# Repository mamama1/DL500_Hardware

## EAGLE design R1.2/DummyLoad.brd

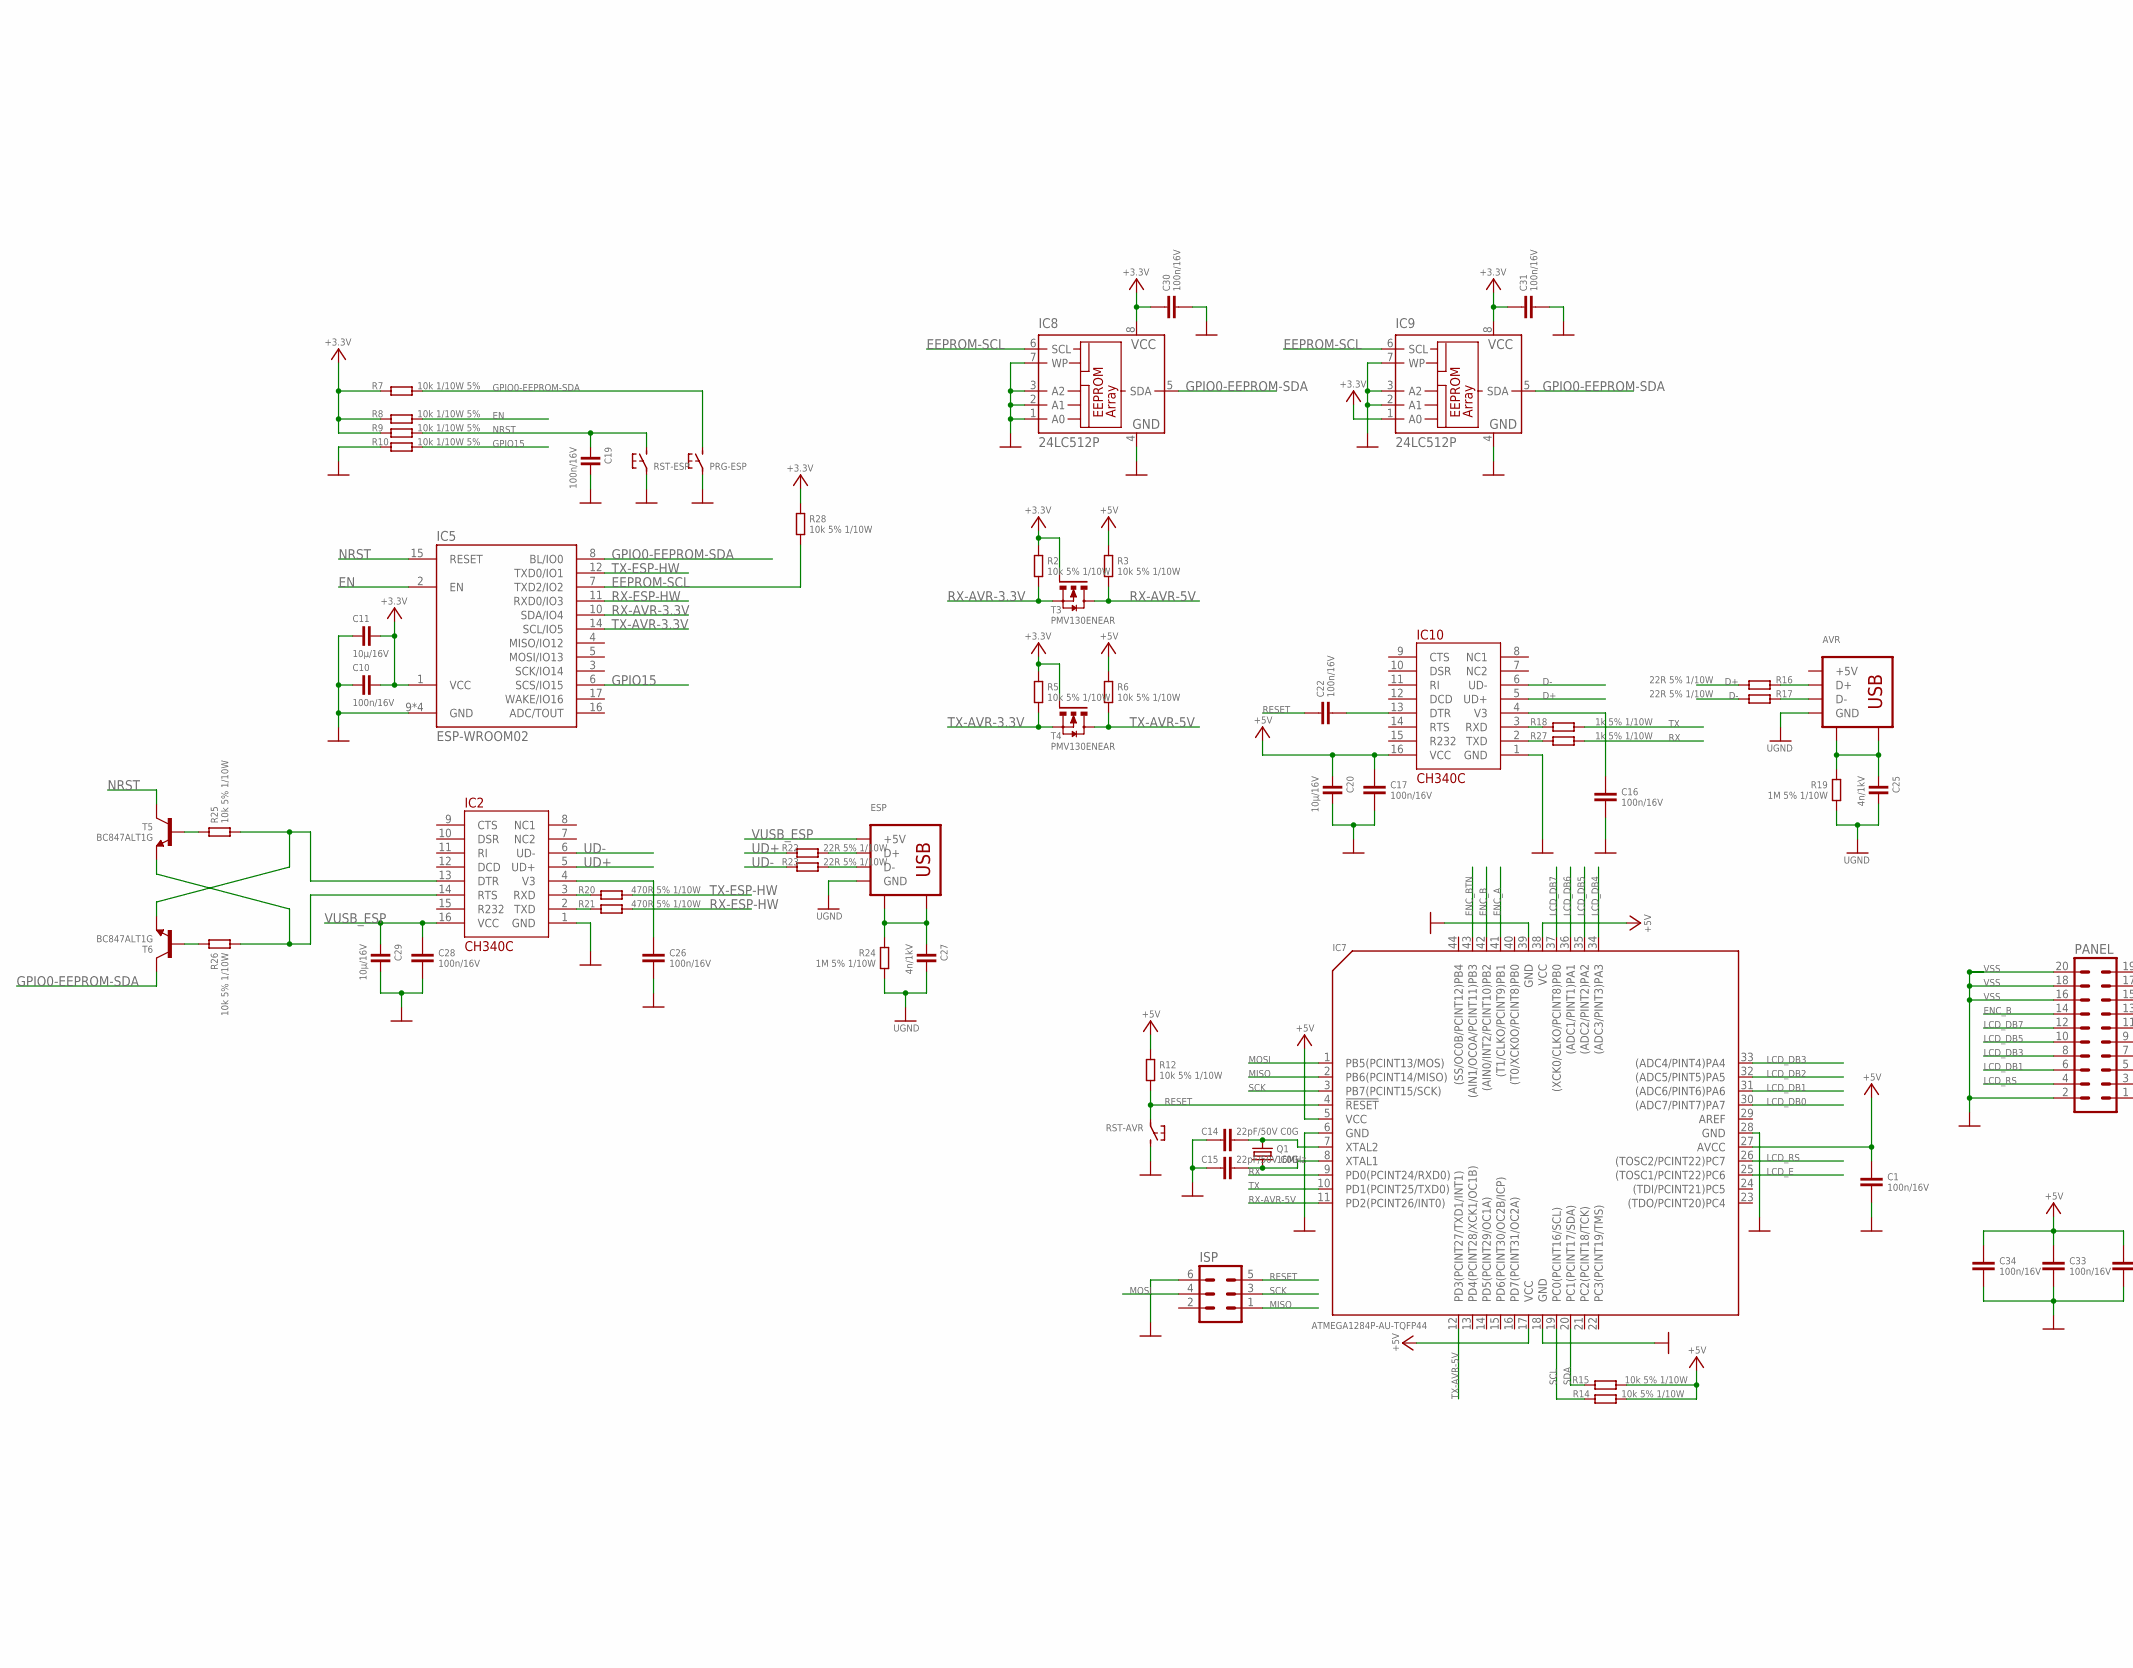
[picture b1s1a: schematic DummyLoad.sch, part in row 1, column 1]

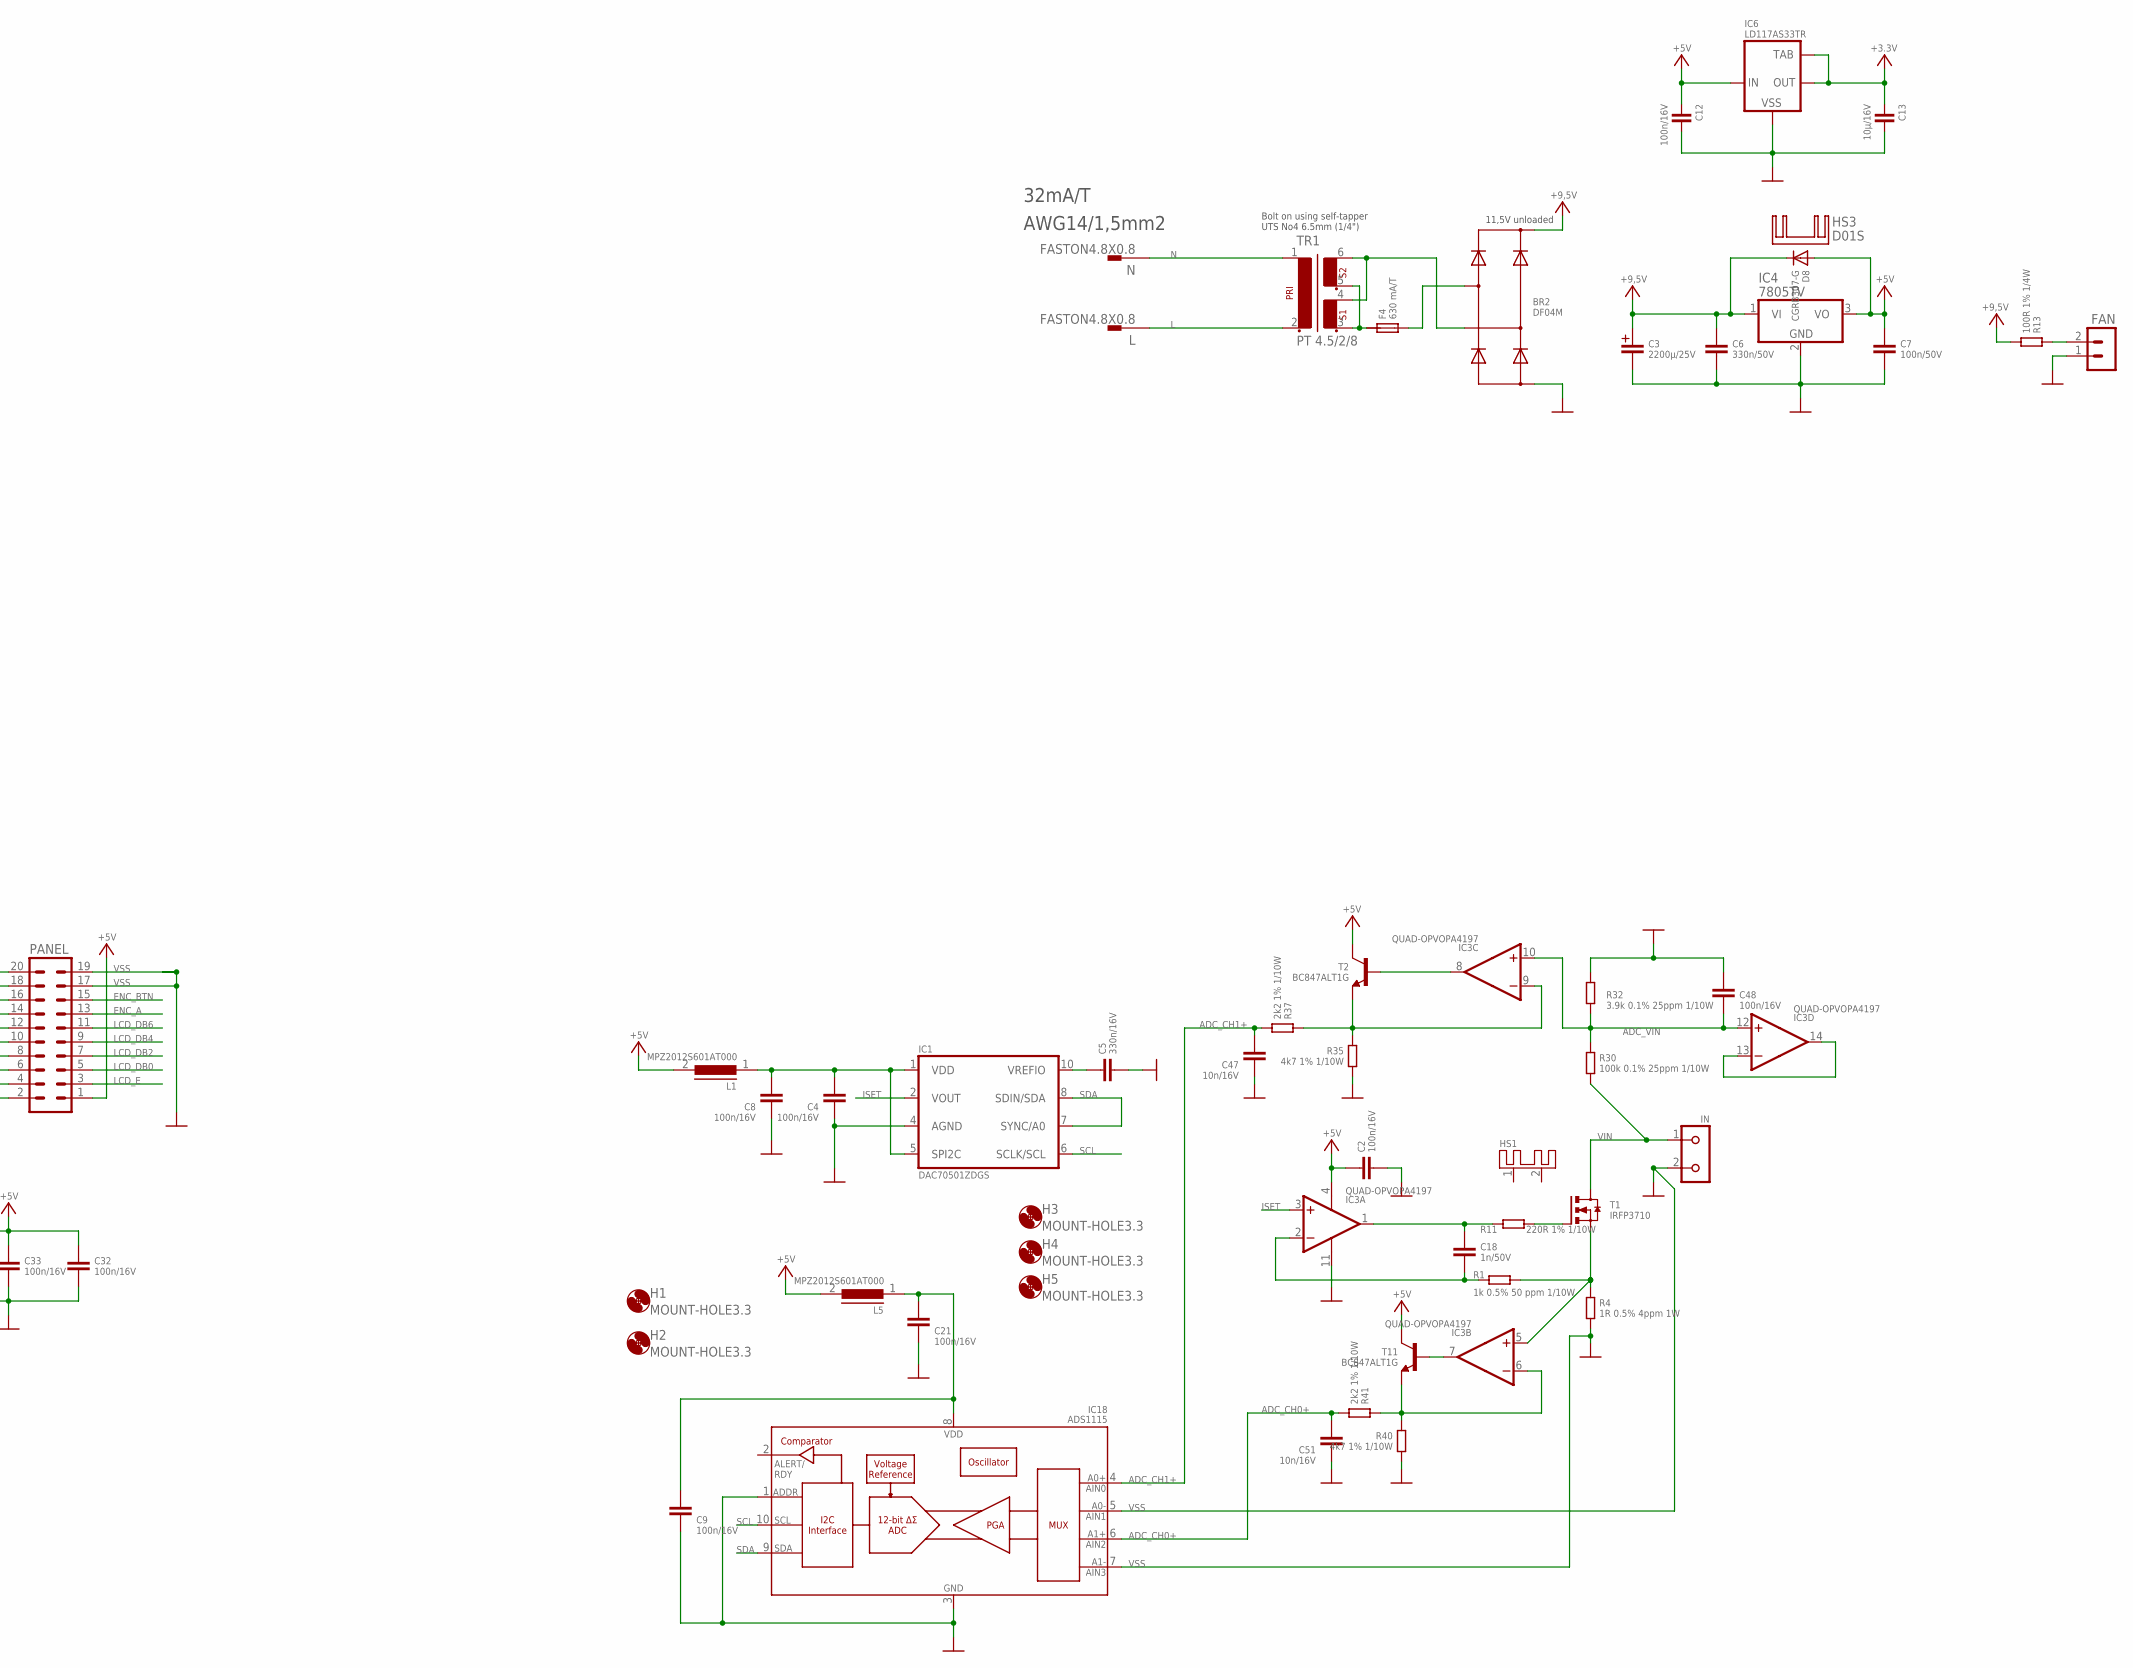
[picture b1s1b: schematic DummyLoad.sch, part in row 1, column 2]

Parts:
AVR: USBUSB-B; USB-B
BR2: DF04M; BR-DIL2
C1, C2, C4, C8, C9, C16, C17, C21, C22, C26, C28, C30, C31, C32, C33, C34, C48: 100n/16V; 0805
C3: 2200µ/25V; C+/5/12.5
C5: 330n/16V; 0805
C6: 330n/50V; 0805
C7: 100n/50V; 0805
C10, C12, C19: 100n/16V; C0805
C11, C13, C20, C29: 10µ/16V; C1210
C14, C15: 22pF/50V C0G; 0805
C18: 1n/50V; 0805
C25, C27: 4n/1kV; C1206
C47, C51: 10n/16V; 0805
D8: CGRB307-G; DO214AA-CGRB307-G
ESP: USBUSB-B; USB-B
F4: 630 mA/T; F5X20
FAN: JST-PH-2.0-2P
H1, H2, H3, H4, H5: MOUNT-HOLE3.3; 3,3
HS1: HSCR201-50; CR201-50
HS3: D01S
IC1: DAC70501ZDGS; VSSOP10
IC2, IC10: CH340C; SOP16
IC3: QUAD-OPVOPA4197; SO14
IC4: 7805TV; TO220V
IC5: ESP-WROOM02
IC6: LD117AS33TR; SOT223
IC7: ATMEGA1284P-AU-TQFP44; TQFP44-0.8-9.6X9.6MM
IC8, IC9: 24LC512P; DIL08
IC18: ADS1115; VSSOP10
IN: KL2691311500002; KL2-691311500002
ISP: ML6
L: FASTON4.8X0.8; FASTON-4.8X0.8
L1, L5: MPZ2012S601AT000; C0805K
N: FASTON4.8X0.8; FASTON-4.8X0.8
PANEL: MA10-2
PRG-ESP: TS1B3F-10XX; B3F-10XX
Q1: 16MHz; Q-5X3.2MM-TXC-7A.SERIES
R1: 1k 0.5% 50 ppm 1/10W; C0805K
R2, R3, R5, R6, R12, R14, R15, R25, R26, R28: 10k 5% 1/10W; C0805K
R4: 1R 0.5% 4ppm 1W; R-SHUNT-VSR
R7, R8, R9, R10: 10k 1/10W 5%; C0805K
R11: 220R 1% 1/10W; C0805K
R13: 100R 1% 1/4W; C0805K
R16, R17, R22, R23: 22R 5% 1/10W; C0805K
R18, R27: 1k 5% 1/10W; C0805K
R19, R24: 1M 5% 1/10W; C0805K
R20, R21: 470R 5% 1/10W; C0805K
R30: 100k 0.1% 25ppm 1/10W; C0805K
R32: 3.9k 0.1% 25ppm 1/10W; C0805K
R35, R40: 4k7 1% 1/10W; C0805K
R37, R41: 2k2 1% 1/10W; C0805K
RST-AVR: TS1B3F-10XX; B3F-10XX
RST-ESP: TS1B3F-10XX; B3F-10XX
T1: IRFP3710; TOP3AV
T2, T5, T6, T11: BC847ALT1G; SOT23-BEC
T3, T4: PMV130ENEAR; SOT23
TR1: PT 4.5/2/8; PT/4,5/2/..

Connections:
+3.3V: C10.2, C11.2, C13.1, C30.1, C31.1, IC5.1 (VCC), IC6.2 (OUT), IC6.4 (OUT1), IC8.8 (VCC), IC9.1 (A0), IC9.8 (VCC), R2.1, R5.1, R7.1, R8.1, R9.1, R28.1, T3.1 (G), T4.1 (G)
+5V: C1.1, C2.1, C7.1, C12.1, C17.1, C20.1, C32.1, C33.1, C34.1, D8.A, IC3.4 (V+), IC4.3 (VO), IC6.3 (IN), IC7.5 (VCC), IC7.17 (VCC), IC7.27 (AVCC), IC7.38 (VCC), IC10.16 (VCC), L1.2, L5.2, PANEL.1, R3.1, R6.1, R12.1, R14.2, R15.2, T2.C, T11.C
+9,5V: BR2.DC+, C3.+, C6.1, D8.C, IC4.1 (VI), R13.2
ADC_CH0+: C51.1, IC18.6 (AIN2), R41.2
ADC_CH1+: C47.1, IC18.4 (AIN0), R37.2
ADC_VIN: C48.2, IC3.10 (+IN), IC3.12 (+IN), R30.1, R32.2
D+: IC10.5 (UD+), R16.1
D-: IC10.6 (UD-), R17.1
EEPROM-SCL: IC5.7 (TXD2/IO2), IC8.6 (SCL), IC9.6 (SCL), R28.2
EN: IC5.2 (EN), R8.2
ENC_A: IC7.41 ((T1/CLKO/PCINT9)PB1), PANEL.13
ENC_B: IC7.42 ((AIN0/INT2/PCINT10)PB2), PANEL.14
ENC_BTN: IC7.43 ((AIN1/OCOA/PCINT11)PB3), PANEL.15
GPIO0-EEPROM-SDA: IC5.8 (BL/IO0), IC8.5 (SDA), IC9.5 (SDA), PRG-ESP.3 (2), R7.2, T6.C
GPIO15: IC5.6 (SCS/IO15), R10.2
ISET: IC1.2 (VOUT), IC3.3 (+IN)
L: L.A1, L.A2, TR1.2
LCD_DB0: IC7.30 ((ADC7/PINT7)PA7), PANEL.5
LCD_DB1: IC7.31 ((ADC6/PINT6)PA6), PANEL.6
LCD_DB2: IC7.32 ((ADC5/PINT5)PA5), PANEL.7
LCD_DB3: IC7.33 ((ADC4/PINT4)PA4), PANEL.8
LCD_DB4: IC7.34 ((ADC3/PINT3)PA3), PANEL.9
LCD_DB5: IC7.35 ((ADC2/PINT2)PA2), PANEL.10
LCD_DB6: IC7.36 ((ADC1/PINT1)PA1), PANEL.11
LCD_DB7: IC7.37 ((XCK0/CLKO/PCINT8)PB0), PANEL.12
LCD_E: IC7.25 ((TOSC1/PCINT22)PC6), PANEL.3
LCD_RS: IC7.26 ((TOSC2/PCINT22)PC7), PANEL.4
MISO: IC7.2 (PB6(PCINT14/MISO)), ISP.1
MOSI: IC7.1 (PB5(PCINT13/MOS)), ISP.4
N: N.A1, N.A2, TR1.1
unnamed: C18.1, IC3.1 (OUT), R11.1
unnamed: IC3.7 (OUT), T11.B
unnamed: C16.1, IC10.4 (V3)
unnamed: C18.2, IC3.2 (-IN), R1.2
unnamed: IC3.5 (+IN), R1.1, R4.1, T1.E (S)
unnamed: C9.1, C21.1, IC18.8 (VDD), L5.1
unnamed: C5.1, IC1.10 (VREFIO)
unnamed: IC3.8 (OUT), T2.B
unnamed: IC3.13 (-IN), IC3.14 (OUT)
unnamed: AVR.D+, R16.2
unnamed: AVR.D-, R17.2
unnamed: R11.2, T1.B (G)
unnamed: IC10.3 (RXD), R18.1
unnamed: C14.2, IC7.7 (XTAL2), Q1.2
unnamed: C15.2, IC7.8 (XTAL1), Q1.1
unnamed: IC10.2 (TXD), R27.1
unnamed: AVR.SH1, AVR.SH2, C25.1, R19.1
unnamed: C26.1, IC2.4 (V3)
unnamed: IC2.3 (RXD), R20.1
unnamed: IC2.2 (TXD), R21.1
unnamed: ESP.D+, R22.2
unnamed: ESP.D-, R23.2
unnamed: C27.1, ESP.SH1, ESP.SH2, R24.1
unnamed: R25.1, T5.B
unnamed: R26.1, T6.B
unnamed: C22.2, IC10.13 (DTR)
unnamed: BR2.AC1, F4.3 (2), F4.4 (2)
unnamed: IC2.14 (RTS), R26.2, T5.E
unnamed: IC2.13 (DTR), R25.2, T6.E
unnamed: F4.1, F4.2 (1), TR1.3, TR1.5
unnamed: BR2.AC2, TR1.4, TR1.6
unnamed: FAN.2, R13.1
unnamed: IC3.9 (-IN), R35.1, R37.1, T2.E
unnamed: IC3.6 (-IN), R40.1, R41.1, T11.E
NRST: C19.1, IC5.15 (RESET), R9.2, RST-ESP.3 (2), T5.C
RESET: C22.1, IC7.4 (!RESET), ISP.5, R12.2, RST-AVR.1
RX: IC7.9 (PD0(PCINT24/RXD0)), R27.2
RX-AVR-3.3V: IC5.10 (SDA/IO4), R2.2, T3.2 (S)
RX-AVR-5V: IC7.11 (PD2(PCINT26/INT0)), R3.2, T3.3 (D)
RX-ESP-HW: IC5.11 (RXD0/IO3), R21.2
SCK: IC7.3 (PB7(PCINT15/SCK)), ISP.3
SCL: IC1.6 (SCLK/SCL), IC7.19 (PC0(PCINT16/SCL)), IC18.10 (SCL), R14.1
SDA: IC1.7 (SYNC/A0), IC1.8 (SDIN/SDA), IC7.20 (PC1(PCINT17/SDA)), IC18.9 (SDA), R15.1
TX: IC7.10 (PD1(PCINT25/TXD0)), R18.2
TX-AVR-3.3V: IC5.14 (SCL/IO5), R5.2, T4.2 (S)
TX-AVR-5V: IC7.12 (PD3(PCINT27/TXD1/INT1)), R6.2, T4.3 (D)
TX-ESP-HW: IC5.12 (TXD0/IO1), R20.2
UD+: IC2.5 (UD+), R22.1
UD-: IC2.6 (UD-), R23.1
UGND: AVR.GND, C25.2, C27.2, ESP.GND, R19.2, R24.2
VDD: C4.1, C8.1, IC1.1 (VDD), IC1.5 (SPI2C), L1.1
VIN: IN.1, R30.2, T1.C (D)
VSS: BR2.DC-, C1.2, C2.2, C3.-, C4.2, C5.2, C6.2, C7.2, C8.2, C9.2, C10.1, C11.1, C12.2, C13.2, C14.1, C15.1, C16.2, C17.2, C19.2, C20.2, C21.2, C26.2, C28.2, C29.2, C30.2, C31.2, C32.2, C33.2, C34.2, C47.2, C48.1, C51.2, FAN.1, IC1.4 (AGND), IC2.1 (GND), IC3.11 (V-), IC4.2 (GND), IC5.9 (GND), IC5.13 (GND), IC5.18 (GND), IC5.TP (GND), IC6.1 (VSS), IC7.6 (GND), IC7.18 (GND), IC7.28 (GND), IC7.39 (GND), IC8.1 (A0), IC8.2 (A1), IC8.3 (A2), IC8.4 (GND), IC8.7 (WP), IC9.2 (A1), IC9.3 (A2), IC9.4 (GND), IC9.7 (WP), IC10.1 (GND), IC18.1 (ADDR), IC18.3 (VSS), IC18.5 (AIN1), IC18.7 (AIN3), IN.2, ISP.6, PANEL.2, PANEL.16, PANEL.17, PANEL.18, PANEL.19, PANEL.20, PRG-ESP.1, R4.2, R10.1, R32.1, R35.2, R40.2, RST-AVR.3 (2), RST-ESP.1
VUSB_ESP: C28.1, C29.1, ESP.+5V, IC2.16 (VCC)

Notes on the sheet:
11,5V unloaded
AWG14/1,5mm2
32mA/T
Bolt on using self-tapper UTS No4 6.5mm (1/4")

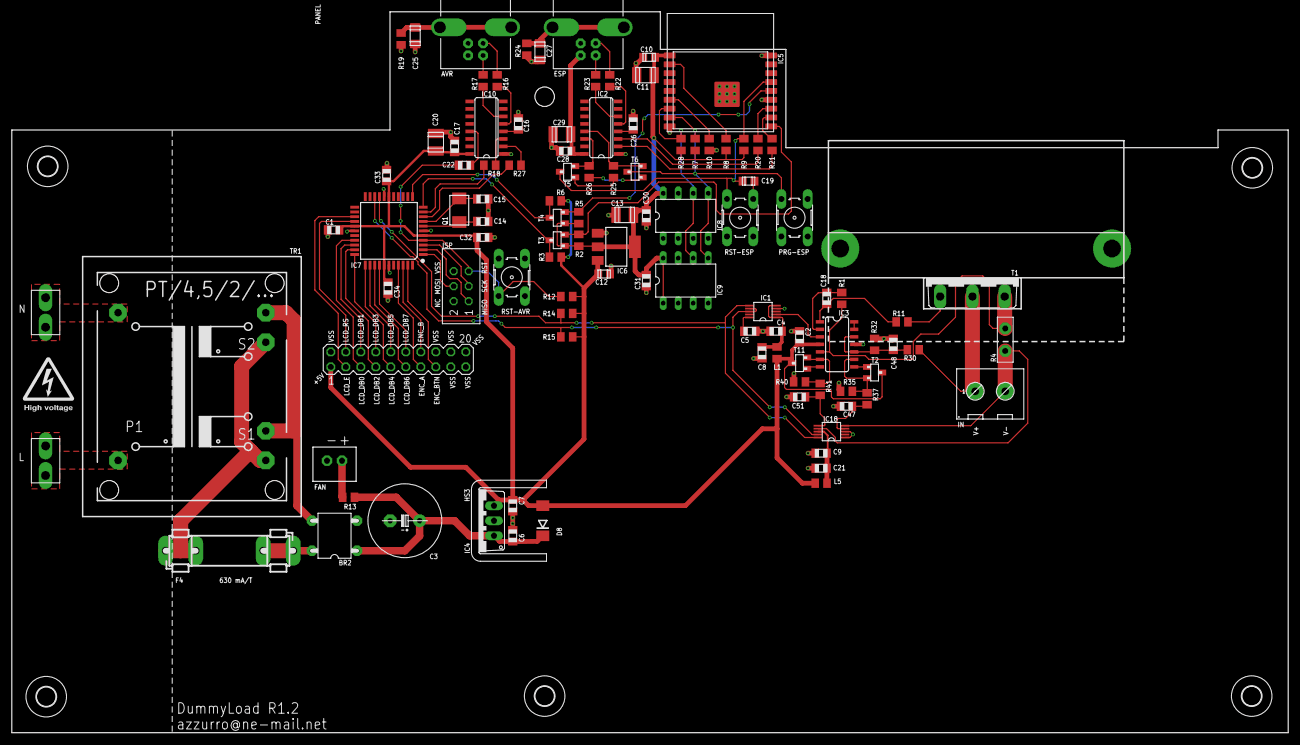
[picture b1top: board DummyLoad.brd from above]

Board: 2 copper layers, 216.0 x 122.0 mm, 116 parts (0 on the bottom side), 84 nets.

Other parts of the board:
U$1: CASE-Z17
U$2: IEC-C14-FUSED-6200.2200
U$3: FAN60X25
U$4: SWITCH-ROCKER-1858.1103

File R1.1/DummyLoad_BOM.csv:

"Qty";"Value";"Device";"Package";"Parts";"Description";"MF";"MPN";"OC_CONRAD";"OC_CONRAD_ADD";"OC_DIGIKEY";"OC_FARNELL";"OC_MOUSER";"OC_MOUSER_ADD";"OC_MOUSER_ADD2";"OC_MOUSER_ALT";"OC_NEWARK";"OC_RS";"OC_RS_ADD";
"1";"";"HSCR201-50";"CR201-50";"HS1";"";"";"";"";"";"";"";"588-CR201-50VE";"588-CLA-TO-21E";"";"";"";"";"";
"1";"";"JST-PH-2.0-2P";"JST-PH-2.0-2P";"FAN";"PIN HEADER";"";"";"";"";"455-1704-ND";"";"";"369-MF60251V21UA99";"";"";"";"";"";
"1";"";"KL2691311500002";"KL2-691311500002";"IN";"Printklemme 2-polig";"";"";"";"";"";"";"710-691311500002";"565-72912-2";"565-6883";"";"";"";"";
"1";"";"MA10-2";"MA10-2";"PANEL";"PIN HEADER";"";"";"";"";"";"unknown";"200-HTSW10907LMD";"";"";"";"unknown";"";"";
"1";"";"ML6";"ML6";"ISP";"HARTING";"";"";"";"";"";"unknown";"200-TSW10307TD";"";"";"";"unknown";"";"";
"3";"";"TS1B3F-10XX";"B3F-10XX";"PRG-ESP, RST-AVR, RST-ESP";"";"";"";"";"";"";"";"653-B3F-1022";"";"";"";"";"";"";
"2";"";"USBUSB-B";"USB-B";"AVR, ESP";"";"";"";"";"";"";"";"";"";"";"";"";"674-1328";"";
"1";"100R 1% 1/4W";"R-SMD0805";"C0805K";"R13";"R";"";"";"";"";"";"";"660-RK73H2ATTD75R0F";"";"";"";"";"";"";
"1";"100k 0.1% 25ppm 1/10W";"R-SMD0805";"C0805K";"R30";"R";"";"";"";"";"";"";"754-RG2012P-104-B-T5";"";"";"";"";"";"";
"3";"100n/16V";"CAPACITOR-0805";"C0805";"C10, C12, C19";"Capacitors";"";"";"";"";"";"";"810-C2012X7R2A104K";"";"";"";"";"";"";
"16";"100n/16V";"CC/0805";"0805";"C1, C2, C4, C8, C9, C16, C17, C20, C21, C22, C23, C26, C28, C30, C31, C48";"Kondensator";"";"";"";"";"";"";"810-C2012X7R2A104K";"";"";"";"";"";"";
"1";"100n/50V";"CC/0805";"0805";"C7";"Kondensator";"";"";"";"";"";"";"810-C2012X7R2A104K";"";"";"";"";"";"";
"4";"10k 1/10W 5%";"R-SMD0805";"C0805K";"R7, R8, R9, R10";"R";"";"";"";"";"";"";"652-CR0805-JW-103ELF";"";"";"";"";"";"";
"11";"10k 5% 1/10W";"R-SMD0805";"C0805K";"R2, R3, R5, R6, R12, R14, R15, R18, R25, R26, R28";"R";"";"";"";"";"";"";"652-CR0805-JW-103ELF";"";"";"";"";"";"";
"2";"10n/16V";"CC/0805";"0805";"C47, C51";"Kondensator";"";"";"";"";"";"";"80-C0805C103K1R";"";"";"";"";"";"";
"4";"10µ/16V";"CAPACITOR-1210";"C1210";"C11, C13, C24, C29";"Capacitors";"";"";"";"";"";"";"963-UMK316BBJ106KL-T";"";"";"";"";"";"";
"1";"16MHz";"Q5X3.2MM-TXC-7A-SERIES";"Q-5X3.2MM-TXC-7A.SERIES";"Q1";"";"";"";"";"";"";"";"717-7A-16.000MAAJ-T";"";"";"";"";"";"";
"2";"1M 5% 1/10W";"R-SMD0805";"C0805K";"R19, R24";"R";"";"";"";"";"";"";"652-CR0805JW-105ELF";"";"";"";"";"";"";
"1";"1R 0.5% 4ppm 1W";"R-SHUNTVSR";"R-SHUNT-VSR";"R4";"";"";"";"";"";"";"";"71-VSRT1R0000DB";"";"";"";"";"";"";
"1";"1k 0.5% 50 ppm 1/10W";"R-SMD0805";"C0805K";"R1";"R";"";"";"";"";"";"";"754-RR1220P-102D";"";"";"";"";"";"";
"1";"1n/50V";"CC/0805";"0805";"C18";"Kondensator";"";"";"";"";"";"";"603-CC805KRX7R0BB102";"";"";"";"";"";"";
"1";"1µ/35V";"CC/0805";"0805";"C32";"Kondensator";"";"";"";"";"";"";"963-UMK212B7105KG-T";"";"";"";"";"";"";
"1";"2200µ/25V";"C+5/12.5";"C+/5/12.5";"C3";"";"";"";"";"";"";"";"667-EEU-FS1E222";"";"";"";"";"";"";
"1";"220R 1% 1/10W";"R-SMD0805";"C0805K";"R11";"R";"";"";"";"";"";"";"652-CR0805FX-2201ELF";"";"";"";"";"";"";
"4";"22R 5% 1/10W";"R-SMD0805";"C0805K";"R16, R17, R22, R23";"R";"";"";"";"";"";"";"652-CR0805JW-220ELF";"";"";"";"";"";"";
"2";"22pF/50V C0G";"CC/0805";"0805";"C14, C15";"Kondensator";"";"";"";"";"";"";"603-CC805JRNPO9BN220";"";"";"";"";"";"";
"2";"24LC512P";"24LC256P";"DIL8";"IC8, IC9";"Serial EEPROM";"MICROCHIP";"24LC256-E/P";"";"";"";"9757970";"579-24LC512-E/P";"";"";"";"92C7169";"";"";
"2";"2k2 1% 1/10W";"R-SMD0805";"C0805K";"R37, R41";"R";"";"";"";"";"";"";"652-CR0805FX-2201ELF";"";"";"";"";"";"";
"1";"3.9k 0.1% 25ppm 1/10W";"R-SMD0805";"C0805K";"R32";"R";"";"";"";"";"";"";"754-RG2012P-392-BT5";"";"";"";"";"";"";
"1";"330n/16V";"CC/0805";"0805";"C5";"Kondensator";"";"";"";"";"";"";"80-C0805C334K5RECTU";"";"";"";"";"";"";
"1";"330n/50V";"CC/0805";"0805";"C6";"Kondensator";"";"";"";"";"";"";"80-C0805C334K5RECTU";"";"";"";"";"";"";
"2";"470R 5% 1/10W";"R-SMD0805";"C0805K";"R20, R21";"R";"";"";"";"";"";"";"652-CR0805FX-4700ELF";"";"";"";"";"";"";
"2";"4k7 1% 1/10W";"R-SMD0805";"C0805K";"R35, R40";"R";"";"";"";"";"";"";"652-CR0805FX-4701ELF";"";"";"";"";"";"";
"2";"4n/1kV";"CAPACITOR-1206";"C1206";"C25, C27";"Capacitors";"";"";"";"";"";"";"581-1206AC392K";"";"";"";"";"";"";
"1";"630 mA/T";"F5X20";"F5X20";"F4";"Sicherung";"";"";"";"";"";"";"693-0751.0110";"";"";"";"";"";"";
"1";"7805TV";"7805TV";"TO220V";"IC4";"Positive VOLTAGE REGULATOR";"";"";"";"";"";"";"511-L7805CV";"";"";"";"";"";"";
"1";"ADS1115";"ADS1015VSSOP10";"VSSOP10";"IC18";"ADS1015 12-BIT ADC";"";"";"";"";"";"";"595-ADS1115IDGSR";"";"";"";"";"";"";
"1";"ATMEGA32U4-AU";"ATMEGA32U4-AU";"TQFP44";"IC7";"Atmel ATmega16U4/32U4 AVR Microcontroller";"";"";"";"";"";"";"556-ATMEGA32U4-AU";"";"";"";"";"";"";
"4";"BC847ALT1G";"T-NPNSOT23-BEC";"SOT23-BEC";"T2, T5, T6, T11";"NPN Transistor";"";"";"";"";"";"";"863-BC847ALT1G";"";"";"";"";"";"";
"1";"CGRB307-G";"DWIDE";"DO214AA-CGRB307-G";"D8";"";"";"";"";"";"";"";"750-CGRB307-G";"";"";"";"";"";"";
"1";"CH340C";"CH340C";"SOP16";"IC2";"";"";"";"";"";"";"";"C84681";"";"";"";"";"";"";
"1";"D01S";"D01S";"D01S";"HS3";"HEATSINK";"";"";"";"";"";"";"532-576802B00";"";"";"";"";"";"";
"1";"DAC70501ZDGS";"DAC70501";"VSSOP10";"IC1";"";"";"";"";"";"";"";"595-DAC70501ZDGS";"";"";"";"";"";"";
"1";"DF04M";"BRDIL2";"BR-DIL2";"BR2";"";"";"";"";"";"";"";"621-DF04M";"";"";"512-DF04M";"";"";"";
"1";"ESP-WROOM02";"ESP-WROOM02";"ESP-WROOM02";"IC5";"Espressif ESP-WROOM-02  and AI-Thinker ESP-12 ESP8266 WiFi/WLAN Module";"";"";"";"";"";"";"356-ESPWROOM02D(4MB)";"";"";"";"";"";"";
"2";"FASTON4.8X0.8";"FASTON4.8X0.8";"FASTON-4.8X0.8";"L, N";"Flachstecker Typ Tyco/Electronics/AMP TAB, FASTON";"";"";"736079";"1022092";"";"unknown";"";"";"";"";"unknown";"";"";
"1";"IRFP3710";"T-NMOSTO247";"TOP3AV";"T1";"Transistor N-Channel MOSFET";"";"";"";"";"";"";"942-IRFP3710PBF";"";"";"";"";"";"";
"1";"LD117AS33TR";"LD117AS33TR";"SOT223";"IC6";"Low drop fixed and adjustable positive voltage regulators 1 A";"";"";"";"";"";"";"511-LD1117AS33";"";"";"";"";"";"";
"6";"MOUNT-HOLE3.3";"MOUNT-HOLE3.3";"3,3";"H1, H2, H3, H4, H5, H6";"MOUNTING HOLE with drill center marker";"";"";"";"";"";"";"";"";"";"";"";"";"";
"2";"MPZ2012S601AT000";"L0805";"C0805K@1";"L1, L5";"High Power Density, High Efficiency, Shielded Inductors";"";"";"";"";"";"";"810-MPZ2012S601AT000";"";"";"";"";"";"";
"2";"PMV130ENEAR";"T-NMOSIRLML2502PBF";"SOT23";"T3, T4";"Transistor N-Channel MOSFET";"";"";"";"";"";"";"771-PMV130ENEAR";"";"";"";"";"";"";
"1";"PT 4.5/2/8";"PT4,5/2/..";"PT/4,5/2/..";"TR1";"TRANSFORMER";"";"";"";"";"";"";"";"";"";"";"";"201-8463";"546-5604";
"1";"QUAD-OPVOPA4197";"QUAD-OPVOPA4197";"SO14";"IC3";"";"";"";"";"";"";"";"595-OPA4197IDR";"";"";"";"";"";"";

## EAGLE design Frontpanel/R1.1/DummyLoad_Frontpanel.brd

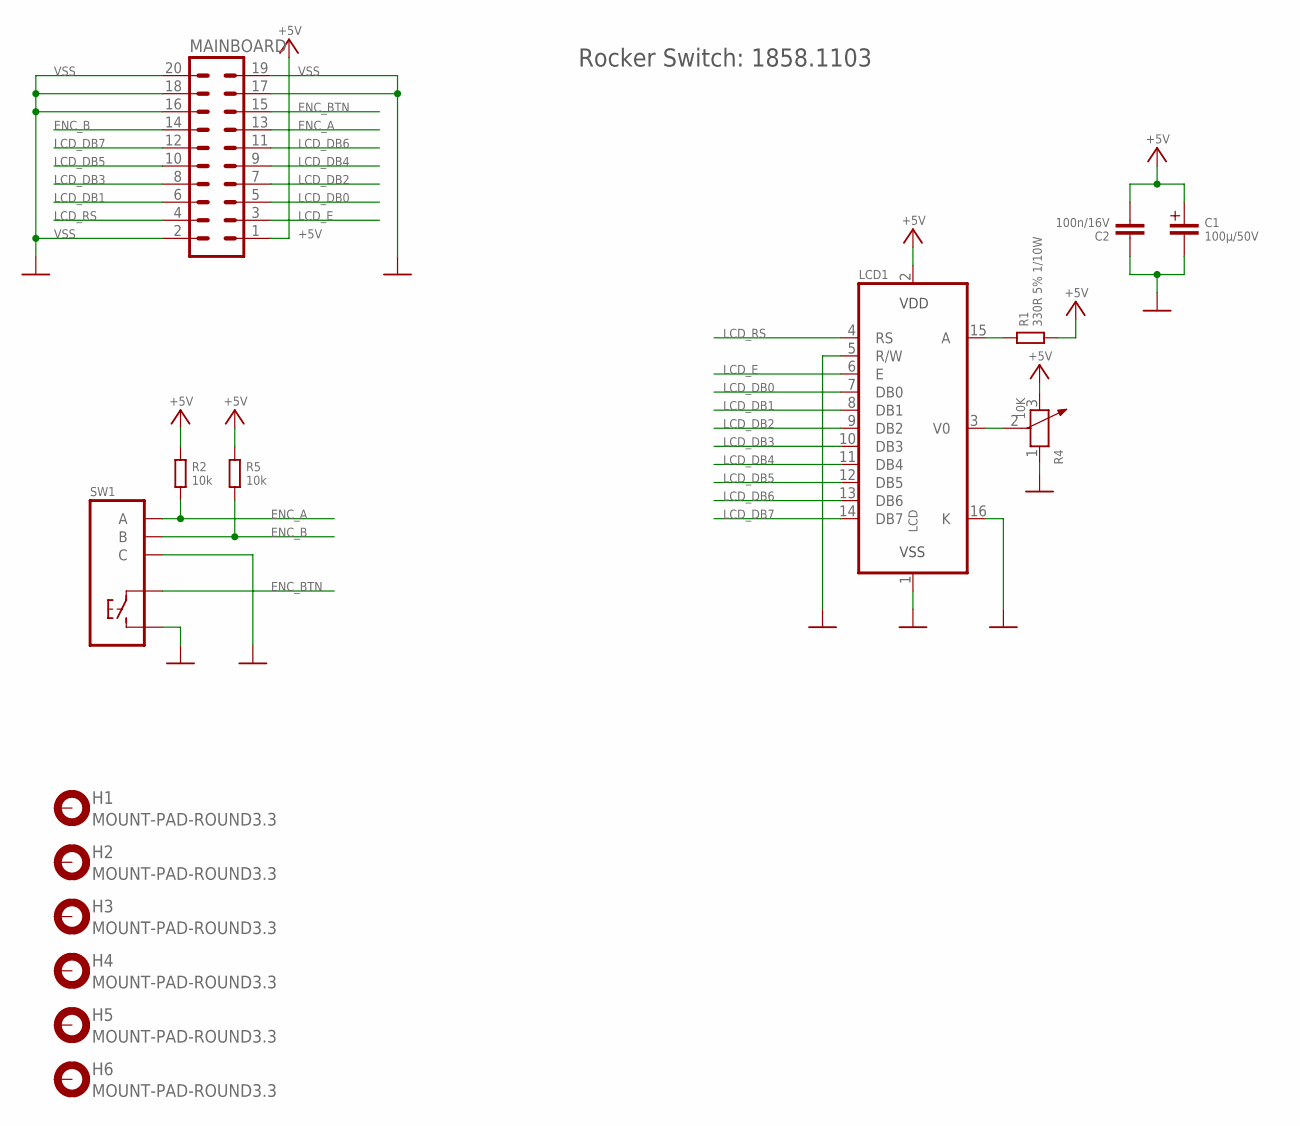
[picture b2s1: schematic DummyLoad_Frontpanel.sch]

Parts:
C1: 100µ/50V; C+/3.5/8
C2: 100n/16V; 0805
H1, H2, H3, H4, H5, H6: MOUNT-PAD-ROUND3.3; 3,3-PAD
LCD1: LCD; DISPLAYTECH-204C
MAINBOARD: MA10-2
R1: 330R 5% 1/10W; C0805K
R2, R5: 10k; C0805K
R4: 10K; ADJR3-7.0X7.0X5.0MM
SW1: EC12E-SW

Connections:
+5V: C1.+, C2.2, LCD1.2 (VDD), MAINBOARD.1, R1.2, R2.1, R4.3, R5.1
ENC_A: MAINBOARD.13, R2.2, SW1.A
ENC_B: MAINBOARD.14, R5.2, SW1.B
ENC_BTN: MAINBOARD.15, SW1.1
LCD_DB0: LCD1.7 (DB0), MAINBOARD.5
LCD_DB1: LCD1.8 (DB1), MAINBOARD.6
LCD_DB2: LCD1.9 (DB2), MAINBOARD.7
LCD_DB3: LCD1.10 (DB3), MAINBOARD.8
LCD_DB4: LCD1.11 (DB4), MAINBOARD.9
LCD_DB5: LCD1.12 (DB5), MAINBOARD.10
LCD_DB6: LCD1.13 (DB6), MAINBOARD.11
LCD_DB7: LCD1.14 (DB7), MAINBOARD.12
LCD_E: LCD1.6 (E), MAINBOARD.3
LCD_RS: LCD1.4 (RS), MAINBOARD.4
unnamed: LCD1.3 (V0), R4.2
unnamed: LCD1.15 (A), R1.1
VSS: C1.-, C2.1, LCD1.1 (VSS), LCD1.5 (R/W), LCD1.16 (K), MAINBOARD.2, MAINBOARD.16, MAINBOARD.17, MAINBOARD.18, MAINBOARD.19, MAINBOARD.20, R4.1, SW1.2, SW1.C

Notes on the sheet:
Rocker Switch: 1858.1103

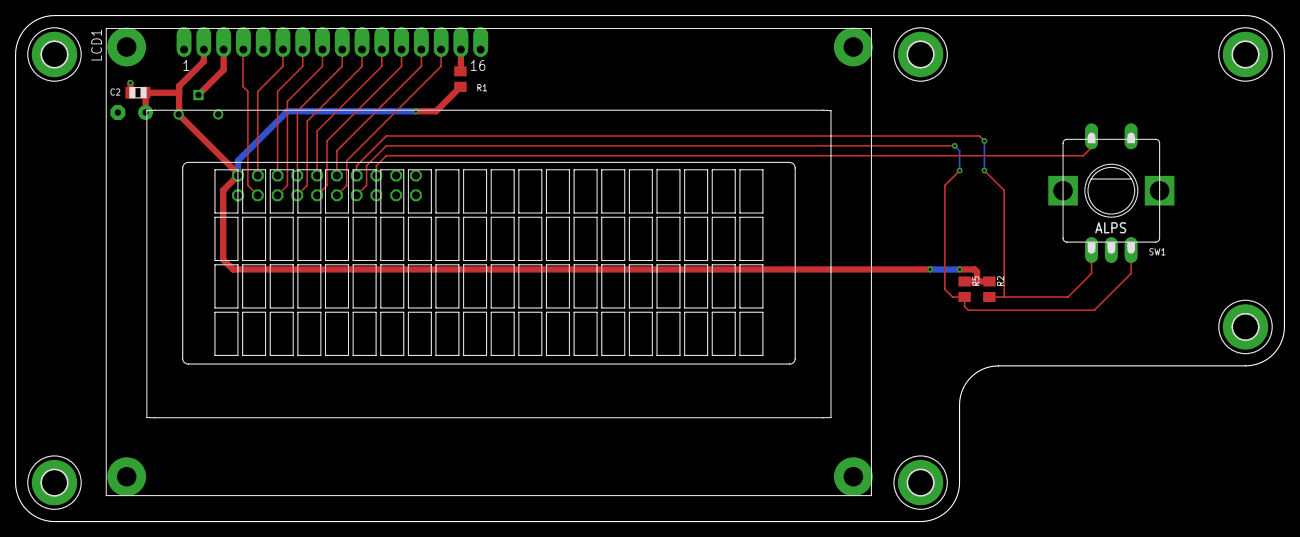
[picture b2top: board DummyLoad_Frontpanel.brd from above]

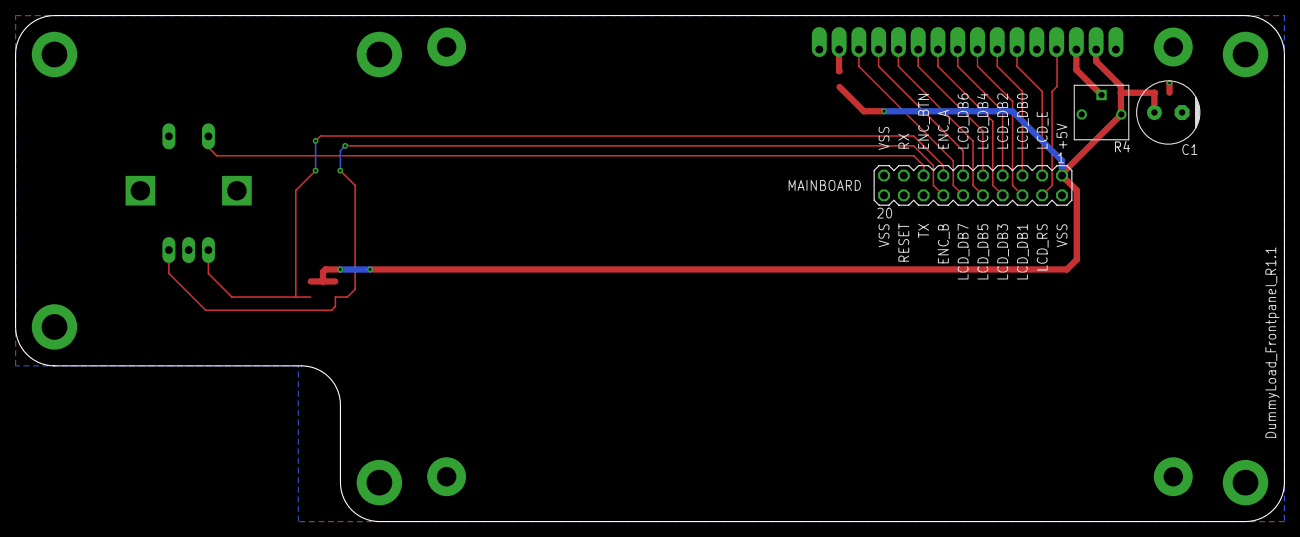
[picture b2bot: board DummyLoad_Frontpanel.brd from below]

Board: 2 copper layers, 163.0 x 65.0 mm, 15 parts (3 on the bottom side), 17 nets.

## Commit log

2021-11-21 add LICENSE.txt
2021-11-23 add rev 1.2
